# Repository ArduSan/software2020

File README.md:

# softwere2020
yo guys gl to everyone

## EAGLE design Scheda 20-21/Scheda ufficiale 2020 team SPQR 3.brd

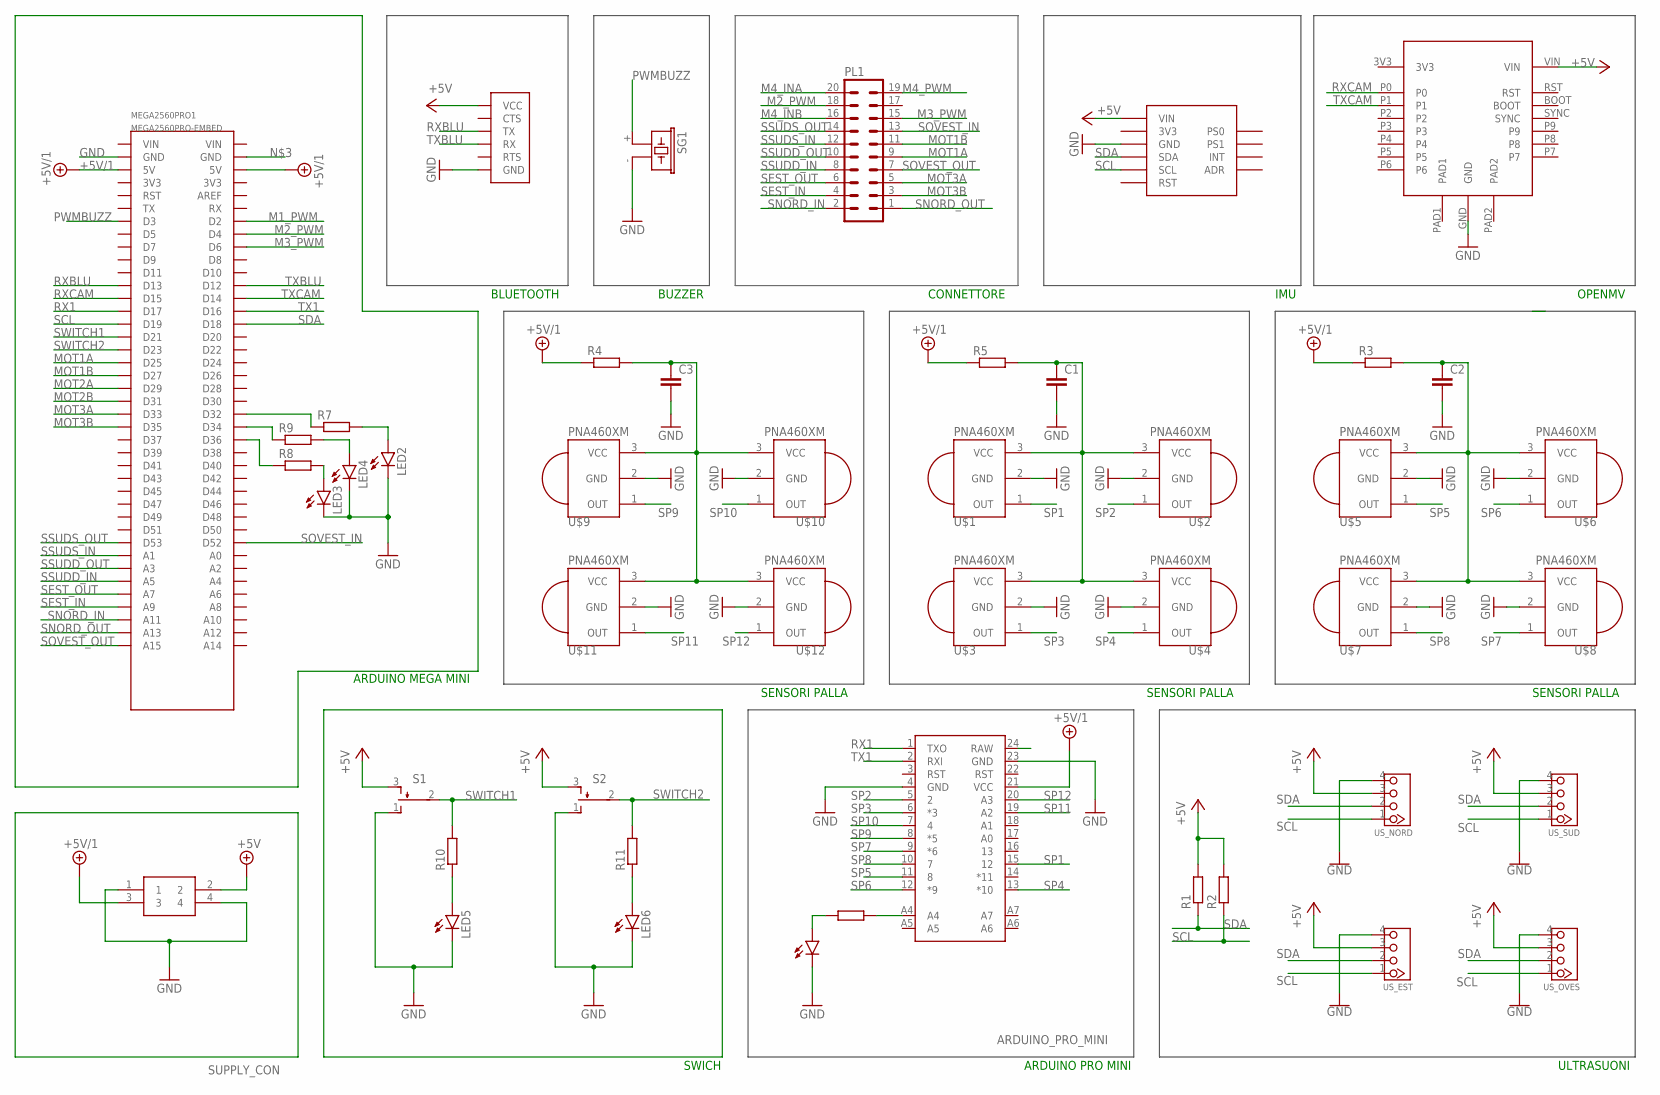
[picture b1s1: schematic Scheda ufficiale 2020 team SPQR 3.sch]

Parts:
ARDUINO_PRO_MINI: ARDUINO_PRO_MINI
C1, C2, C3: C-EUC0805; C0805
LED1, LED2, LED3, LED4, LED5, LED6: LEDCHIPLED_1206; CHIPLED_1206
MEGA2560PRO1: MEGA2560PRO-EMBED
PL1: 20V
R1, R2, R3, R4, R5, R6, R7, R8, R9, R10, R11: R-EU_R0805; R0805
S1, S2: TL38PO; TL3XPO
SG1: F/CM12P
SUPPLY_CON: 39-28-1043
U$1, U$2, U$3, U$4, U$5, U$6, U$7, U$8, U$9, U$10, U$11, U$12: PNA460XM
U$14: BLUESMIRF
U$16: BNO055
U$17: OPENMV_H7
US_EST: TWIG_2.0; 2.0_1X4
US_NORD: TWIG_2.0; 2.0_1X4
US_OVES: TWIG_2.0; 2.0_1X4
US_SUD: TWIG_2.0; 2.0_1X4

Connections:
+5V: R1.2, R2.2, S1.3 (S), S2.3 (S), SUPPLY_CON.2, U$14.VCC, U$16.VIN, U$17.VIN, US_EST.3, US_NORD.3, US_OVES.3, US_SUD.3
+5V/1: ARDUINO_PRO_MINI.21 (VCC), MEGA2560PRO1.5V@1 (5V), MEGA2560PRO1.5V@2 (5V), R3.1, R4.1, R5.1, SUPPLY_CON.3
GND: ARDUINO_PRO_MINI.4 (GND), ARDUINO_PRO_MINI.23 (GND), C1.2, C2.2, C3.2, LED1.C, LED2.C, LED3.C, LED4.C, LED5.C, LED6.C, MEGA2560PRO1.GND@1 (GND), S1.1 (O), S2.1 (O), SG1.- (2), SUPPLY_CON.1, SUPPLY_CON.4, U$1.2 (GND), U$2.2 (GND), U$3.2 (GND), U$4.2 (GND), U$5.2 (GND), U$6.2 (GND), U$7.2 (GND), U$8.2 (GND), U$9.2 (GND), U$10.2 (GND), U$11.2 (GND), U$12.2 (GND), U$14.GND, U$16.GND, U$17.GND, US_EST.4, US_NORD.4, US_OVES.4, US_SUD.4
M1_PWM: MEGA2560PRO1.D2
M2_PWM: MEGA2560PRO1.D4, PL1.18
M3_PWM: MEGA2560PRO1.D6, PL1.15
M4_INA: PL1.20
M4_INB: PL1.16
M4_PWM: PL1.19
MOT1A: MEGA2560PRO1.D25, PL1.9
MOT1B: MEGA2560PRO1.D27, PL1.11
MOT2A: MEGA2560PRO1.D29
MOT2B: MEGA2560PRO1.D31
MOT3A: MEGA2560PRO1.D33, PL1.5
MOT3B: MEGA2560PRO1.D35, PL1.3
unnamed: MEGA2560PRO1.D36, R8.1
unnamed: LED3.A, R8.2
unnamed: MEGA2560PRO1.D34, R9.1
unnamed: ARDUINO_PRO_MINI.A4, R6.2
unnamed: LED1.A, R6.1
unnamed: MEGA2560PRO1.D32, R7.1
unnamed: LED5.A, R10.1
unnamed: LED4.A, R9.2
unnamed: LED6.A, R11.1
unnamed: LED2.A, R7.2
POWERBLOCK1: C2.1, R3.2, U$5.3 (VCC), U$6.3 (VCC), U$7.3 (VCC), U$8.3 (VCC)
POWERBLOCK2: C1.1, R5.2, U$1.3 (VCC), U$2.3 (VCC), U$3.3 (VCC), U$4.3 (VCC)
POWERBLOCK3: C3.1, R4.2, U$9.3 (VCC), U$10.3 (VCC), U$11.3 (VCC), U$12.3 (VCC)
PWMBUZZ: MEGA2560PRO1.D3, SG1.+ (1)
RX1: ARDUINO_PRO_MINI.1 (TXO), MEGA2560PRO1.D17
RXBLU: MEGA2560PRO1.D13, U$14.TX
RXCAM: MEGA2560PRO1.D15, U$17.P0
SCL: MEGA2560PRO1.D19, R2.1, U$16.SCL, US_EST.1, US_NORD.1, US_OVES.1, US_SUD.1
SDA: MEGA2560PRO1.D18, R1.1, U$16.SDA, US_EST.2, US_NORD.2, US_OVES.2, US_SUD.2
SEST_IN: MEGA2560PRO1.A9, PL1.4
SEST_OUT: MEGA2560PRO1.A7, PL1.6
SNORD_IN: MEGA2560PRO1.A11, PL1.2
SNORD_OUT: MEGA2560PRO1.A13, PL1.1
SOVEST_IN: MEGA2560PRO1.D52, PL1.13
SOVEST_OUT: MEGA2560PRO1.A15, PL1.7
SP1: ARDUINO_PRO_MINI.15 (12), U$1.1 (OUT)
SP2: ARDUINO_PRO_MINI.5 (2), U$2.1 (OUT)
SP3: ARDUINO_PRO_MINI.6 (*3), U$3.1 (OUT)
SP4: ARDUINO_PRO_MINI.13 (*10), U$4.1 (OUT)
SP5: ARDUINO_PRO_MINI.11 (8), U$5.1 (OUT)
SP6: ARDUINO_PRO_MINI.12 (*9), U$6.1 (OUT)
SP7: ARDUINO_PRO_MINI.9 (*6), U$8.1 (OUT)
SP8: ARDUINO_PRO_MINI.10 (7), U$7.1 (OUT)
SP9: ARDUINO_PRO_MINI.8 (*5), U$9.1 (OUT)
SP10: ARDUINO_PRO_MINI.7 (4), U$10.1 (OUT)
SP11: ARDUINO_PRO_MINI.19 (A2), U$11.1 (OUT)
SP12: ARDUINO_PRO_MINI.20 (A3), U$12.1 (OUT)
SSUDD_IN: MEGA2560PRO1.A5, PL1.8
SSUDD_OUT: MEGA2560PRO1.A3, PL1.10
SSUDS_IN: MEGA2560PRO1.A1, PL1.12
SSUDS_OUT: MEGA2560PRO1.D53, PL1.14
SWITCH1: MEGA2560PRO1.D21, R10.2, S1.2
SWITCH2: MEGA2560PRO1.D23, R11.2, S2.2
TX1: ARDUINO_PRO_MINI.2 (RXI), MEGA2560PRO1.D16
TXBLU: MEGA2560PRO1.D12, U$14.RX
TXCAM: MEGA2560PRO1.D14, U$17.P1

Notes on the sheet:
BUZZER
IMU
SENSORI PALLA
BLUETOOTH
ARDUINO PRO MINI
ULTRASUONI
SWICH
ARDUINO MEGA MINI
CONNETTORE
OPENMV

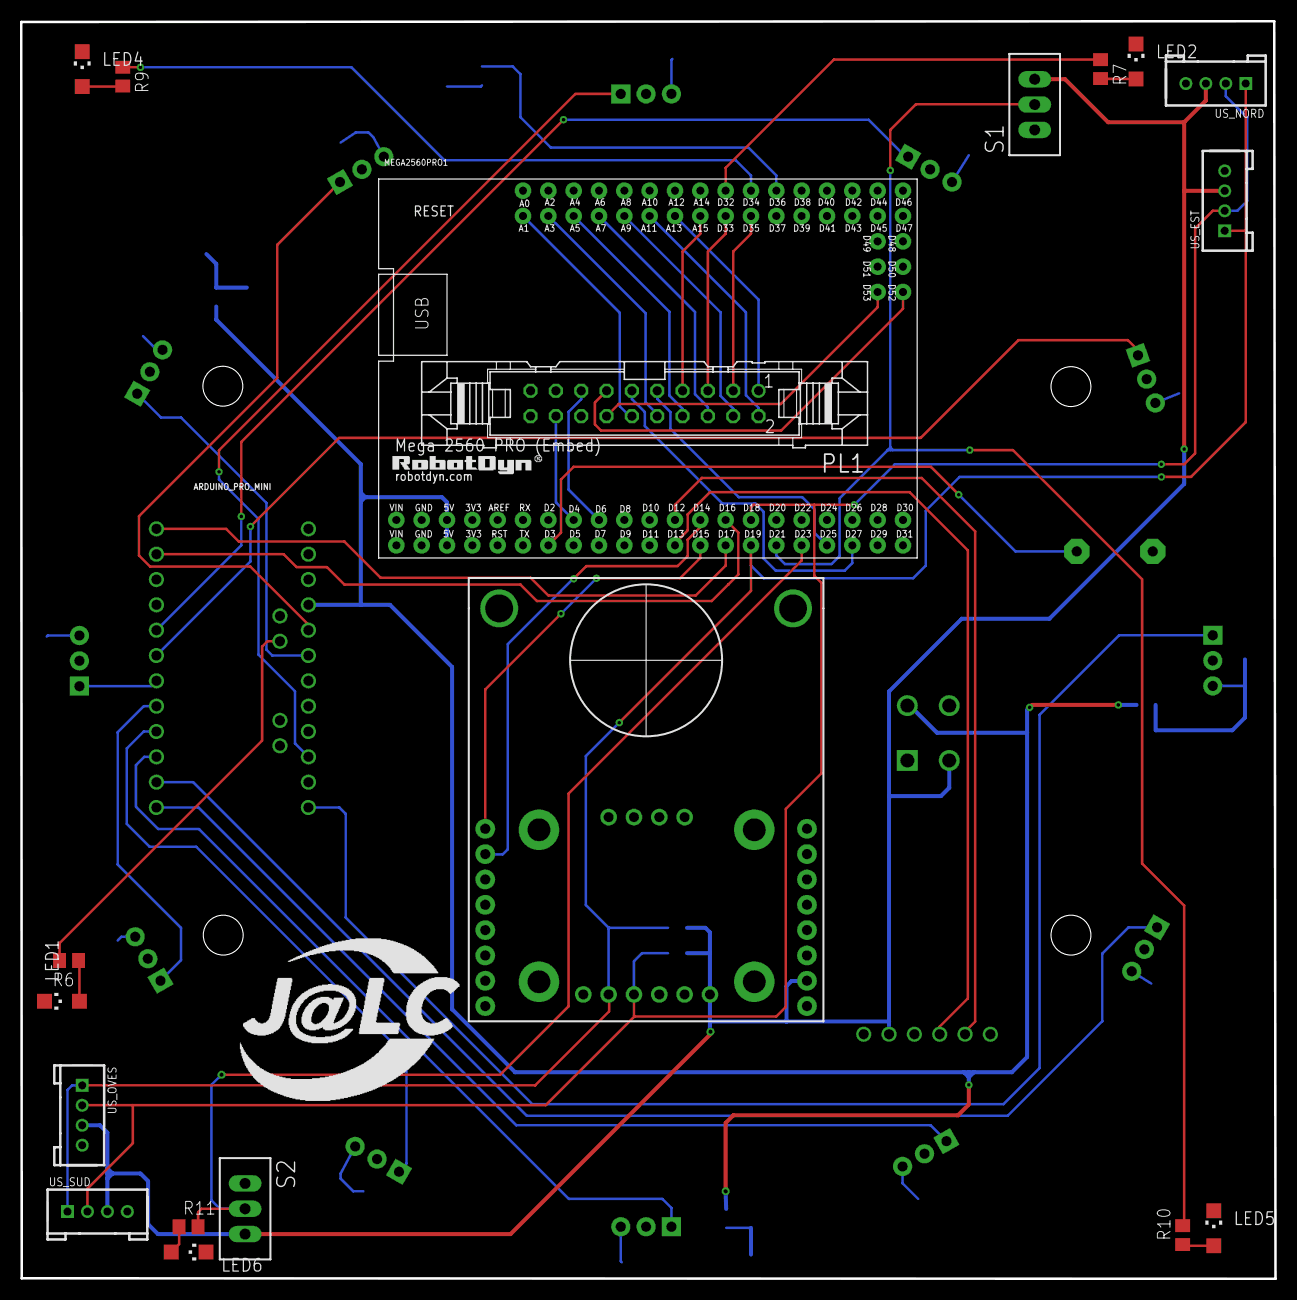
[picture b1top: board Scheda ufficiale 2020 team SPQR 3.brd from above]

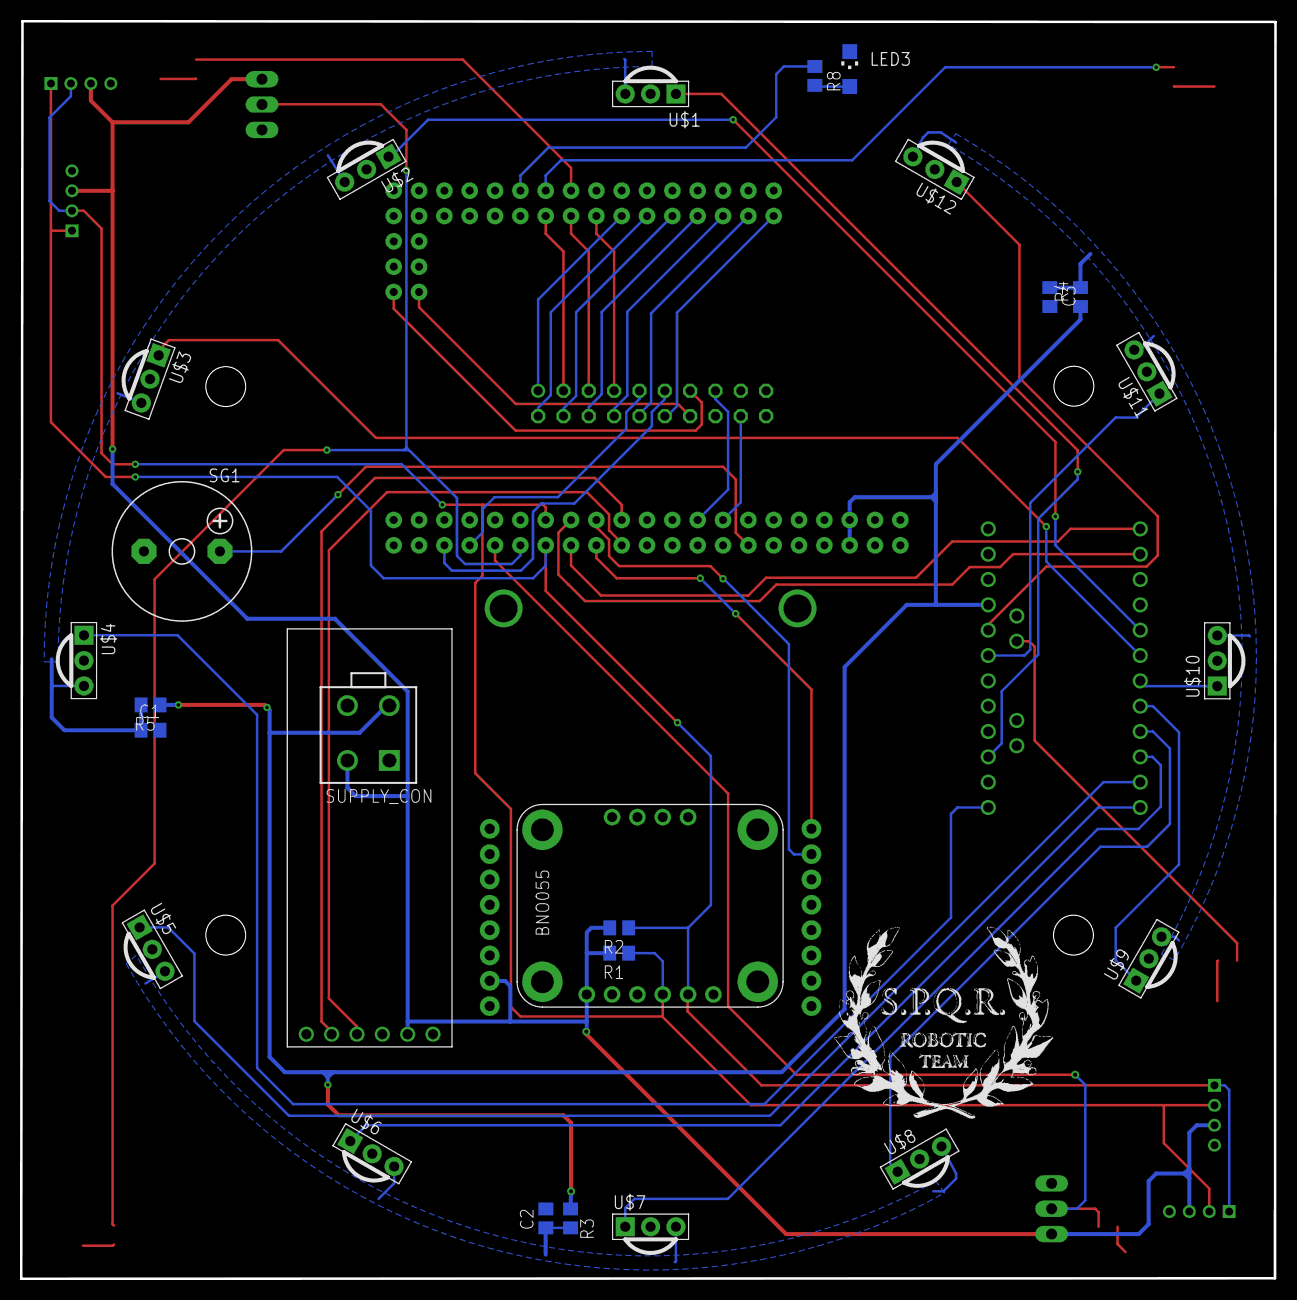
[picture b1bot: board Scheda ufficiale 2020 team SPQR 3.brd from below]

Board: 2 copper layers, 125.8 x 126.1 mm, 46 parts (26 on the bottom side), 55 nets.

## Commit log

2020-01-16 this is the attack
2020-01-16 movement
2020-01-20 yo guys
2020-01-22 nuovo attaccante
2020-02-03 Robot.try
2020-02-05 linee.try 2.0
2020-02-26 codice robot 2020
2020-02-26 cartella per fare delle prove che poi verranno implementate nel main se buone
2020-11-25 aggiornato
2020-12-16 lista pin
2021-05-05 ponte

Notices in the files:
parts and their libraries:
SparkFun-Boards: Licensing: Creative Commons ShareAlike 4.0 International - https://creativecommons.org/licenses/by-sa/4.0
